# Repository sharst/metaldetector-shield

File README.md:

# metaldetector-shield
Hardware and Software for a custom built metaldetector + pressure sensing shield.
This shield was used in a robotics project for contactless navigation (see https://www.youtube.com/watch?v=rSrG_VnvrPk). 
The hardware and software were jointly developed by Simon Harst and Stefan Brüwer.

## It features:
* connection of up to 8 coils which emit and receive electromagnetical impulses
* connection of up to 8 pressure sensors to detect air pulses
* 24V connection with on-board conversion to 5V for the microcontroller
* on-board CAN-Controller to connect the board to a CAN-bus
* chaining possibility to connect two or more boards together for infinite extension
* a ROS example to use it in your robotics application: [www.github.com/sharst/metaldetector-ros](https://github.com/sharst/metaldetector-ros)

## What you can do with it:
* Contactlessly detect metal objects in the vicinity (distance depends on the coil and object used)
* build a rig of 8, 16 or more coils by chaining several boards together
* detect changes in air pressure (in our case upon collision inside an inflateable bumper)
* send all the information on a CAN or serial bus

The board and all accompanying software is fully open source, so you can get involved, too!

## Hardware setup
### How does this work?
The heart of this shield is an arduino microcontroller, which rapidly triggers 8 rigs of transistors connected to coils. From the impulse of current, the coils generate an electromagnetical impulse. In case there is metal in front of the coil, it will reflect part of the impulse which in turn can be sensed by the coil. The weaker echo of the impulse is again converted to current in the coil, which is measured by an ADC on the board. If you want to see a typical response as measured by the ADC, check out the coil response gif below (--> Configuration files). The board sums up the response. This sum can be used to infer whether a metal object is present and how far away it is.

In addition, the shield can measure impact in terms of air pressure. To do that it constantly measures a rolling average of up to 8 air pressure sensors independently. In case it measures a spike of air pressure above a threshold, it emits a custom message.

This is what needs to be done to get one board running (no chaining):
* Solder at least one sensing coil to the COIL_GND and COIL_0 inputs (for more information, check out --> "A note on the coils"
* (Optionally) connect one BMP180-pressure sensor to one of the pressure inputs
* Connect the arduino on the board to your PC and flash the current firmware
* Set jumper J1 to set the board to MASTER mode
* Set jumper J2 to disable chaining
* In case you do not have a coil/capacitor installed at the 24V input, set jumper J3 to bridge the coil connector
* Connect 24V to one of the 24V ports
* The values of the coils are being output on the serial port now (115200baud)

### To enable chaining
Chaining allows you to connect two boards together. The impulses of the coils will influence one another. Therefore you should not operate two coils close together if you want accurate results. The metaldetector board already takes care that up to 8 coils are fired independently in a row and do not influence each other. If you need more than 8 coils, you can use chaining. Chaining uses an additional signal line between two boards, and the boards will take care to always fire their coils alternatingly.
* Remove jumper J2 to enable chaining
* Set jumper J1 on one board to make it the chaining MASTER. Remove the jumper on all other boards to make them slaves
* You can directly chain the 24V power source as well by connecting the secondary 24V-port to the next board
* Connect to signal wires between the boards. The first one should go from output (>) on board 1 to input (<) on board 2. The second one goes from input (<) on board 1 to output (>) on board 2.
* If you want to connect more than two boards together, connect them in a circle, always taking care that the output goes to the input of the next board, and the input is connected to the output of the previous board.
* If you are using the CAN bus, make sure that the boards are using unique CAN addresses (set them in metaldetector-shield.ino --> TX_CAN_ID and RX_CAN_ID)

### How to produce the boards
* We always ordered our boards at PCB-Pool (in Germany). They accept the kicad-files given in the hardware folder directly as input. 
* You can order the entire BOM on farnell, including the wire for the coils. Check out the BOM in the hardware folder.

### A word on the coils
The coils are key when it comes to which objects can be detected. Here's a few notes:
* The larger the coil diameter, the less focused the impulse will be. In general you get a weaker response with larger coils, but also you cover less area
* We tested both with round and rectangular coils, both worked great.
* The more impedance, the less current flow you will get at the fixed 24V, which means less stronger impulses and responses. But it also means less power consumption.
* The more windings the coil has, the stronger the impulse. But also you will naturally get higher impedance with more windings.
* you will have to experiment to find the best tradeoff for your application. In our case it was a coil from 0.4mm wire with 150 windings equalling to ~11 Ohm.

### A note on the pressure sensors
* We ordered the BMP180 sensors on ebay. Note that there are several versions. The boards we used are 1cm x 1.2cm in size. We hand-crimped the cables to connect them via the JST-plugs.
* If you want to use pressure sensors in an outdoor environment, water resistance is key. We used two cable glands connected together to create an air- and water-tight case. We connected an air tube from the one side which guided the air impulse from the bumper cushion into the case (blue arrow). On the other end we connected the air pressure sensor (red arrow). [See image here.](https://github.com/sharst/metaldetector-shield/blob/master/images/air_pressure_connector.jpg).
* For extra water resistance, it is possible to put the pressure sensor into a ballon before inserting it into the cable gland. [See image here.](https://github.com/sharst/metaldetector-shield/blob/master/images/air_pressure_connector_balloon.jpeg)

## Software setup
We've tried to make the software setup as easy as possible for you. Therefore, all the software needed is bundled in this repository, either directly or by submodules.

### To get the arduino running
```
# Go anywhere where you want to check out this repo
cd ~
git clone https://github.com/sharst/metaldetector-shield
cd metaldetector-shield
# Get all the contained submodules
git submodule init 
git submodule update
# The repository contains an arduino folder. This is basically an arduino sketchbook setup and ready to go. First backup your current one:
mv ~/sketchbook ~/sketchbook_bckp
# Now link the one from the repository with a symbolic link. This means you can still use and manage the repository in the original location, but arduino will find your files.
ln -s ~/metaldetector-shield/arduino ~/sketchbook
```
* Open the arduino IDE (tested with v 1.6.9)
* Select Tools --> Board --> Arduino Nano
* Tools --> Programmer --> AVR ISP
* File --> Open --> ~/sketchbook/arduino/metaldetector_shield.ino
* Upload
* Open Serial Console, set it to 115200 baud, watch the output.

### Overview of the software
./arduino: Contains all the software relevant to the arduino (i.e. the firmware and all libraries)
./PythonLivePlotting: A library to do dynamical plots and updates of figures

#### Configuration files
board_v23.h : Contains mostly pin settings (hardwired on the board, don't change them!). You can also set some identifiers on where pressure and heartbeat signals get send on the CAN-BUS, and the identifier to switch coils.  
metaldetector-shield.ino: The main sketch for upload. Contains some interesting settings:
  * TX_CAN_ID: The CAN ID used for writing messages on the bus. If you are using several boards on the same bus, make sure this is unique for each board.
  * RX_CAN_ID: The ID that this board listens on for messages on the bus. You can dynamically switch some functionalities on the board by sending messages. Make sure this ID is unique for this board.
  * DEBUG: Whether or not to output information on the serial bus.
  * COMM_TIMEOUT: How many ms to wait for a signal from the slave board in chaining mode
  * DEBUG_RAW_ADC_COIL: Only works when DEBUG==true. This will output the raw measurements of the given coil as sampled by the ADC. Run python plot_raw_coil.py to visualize these values. This is a sample output where we approach a metal object to the coil:

  * DEBUG_RAW_PRESSURE: Only works when DEBUG==true. This will output the raw measurements of the given pressure sensor. Run python plot_raw_pressure.py to visualize these values. This is a sample output where we register several bumper hits on the given pressure sensor. In red are detected collisions.

#### Typical operation mode
Check out the loop-function in the main sketch. A loop consists of the following steps:
* If coils are enabled, trigger each coil once and read out the results
* we want to average over several measurements. coil.data_ready() goes to True as soon as we have collected this amount of measurements
* In case some coil data is ready we will output it on the serial bus as a four-byte message, which will be in the format ```[40 (COIL_REGISTER set in board_v23.h), [0-7] (coil_index), highbyte(value), lowbyte(value)]```
* The communication state is toggled so the next board can start measuring
* We now sample the pressure sensors. If one of them transitions a threshold value, we encode this information bitwise. For instance, if pressure sensors 2 and 4 have surpassed the threshold value since the last call, get_bumper_transitions will output 0b00010100 (the second and fourth bit are True).
* We now send out the string "BUMPER" on the serial bus. On the CAN-bus we will send the bitcoded value, this time in the format ```[25 (PRESSURE_REGISTER set in board_v23.h), 0, highbyte(bitcode), lowbyte(bitcode)]```.
* We send out a heartbeat message on the CAN bus. This message contains the information on which ports some pressure sensors are connected and whether the metal sensing functionality is currently switched on. Which ports are currently connected to pressure sensors is again encoded bitwise, i.e. 0b10001001 means that there are sensors connected on the first, fourth and eigth connector on the board. A heartbeat message has the format ```[30 (HEARTBEAT_REGISTER set in board_v23.h), bitwise encoding of connected sensors, (1 or 0 whether coils are enabled)]```

#### Getting the CAN bus running
* In order to interface with a CAN bus from a computer, you typically need a CAN to USB converter. We had some eccellent results with the [USBtin](https://www.fischl.de/usbtin/). It is open source, has a superb interface, a loving maintainer and can be ordered readily assembled.
* In order to connect it, just connect the HIGH, LOW and GND (marked as "T" on the USBtin) lines between the two boards. 
* If you want to connect more metaldetector boards, there are two CAN connectors on each one: One coming in, one going out.
* In addition, you need one termination resistor somewhere on the bus, typically on the last element of the bus chain. If this last element is a metaldetector board, you can simply set jumper J4 to enable the termination resistor.
* Connect the USBTin to your computer, open the interface and set it to 500kbps and see the messages from the board coming in. 
* There is also a ROS driver available which directly interfaces the metaldetector-board to ROS messages [www.github.com/sharst/metaldetector-ros](www.github.com/sharst/metaldetector-ros)

## Summary: Information flow from the metaldetector-shield

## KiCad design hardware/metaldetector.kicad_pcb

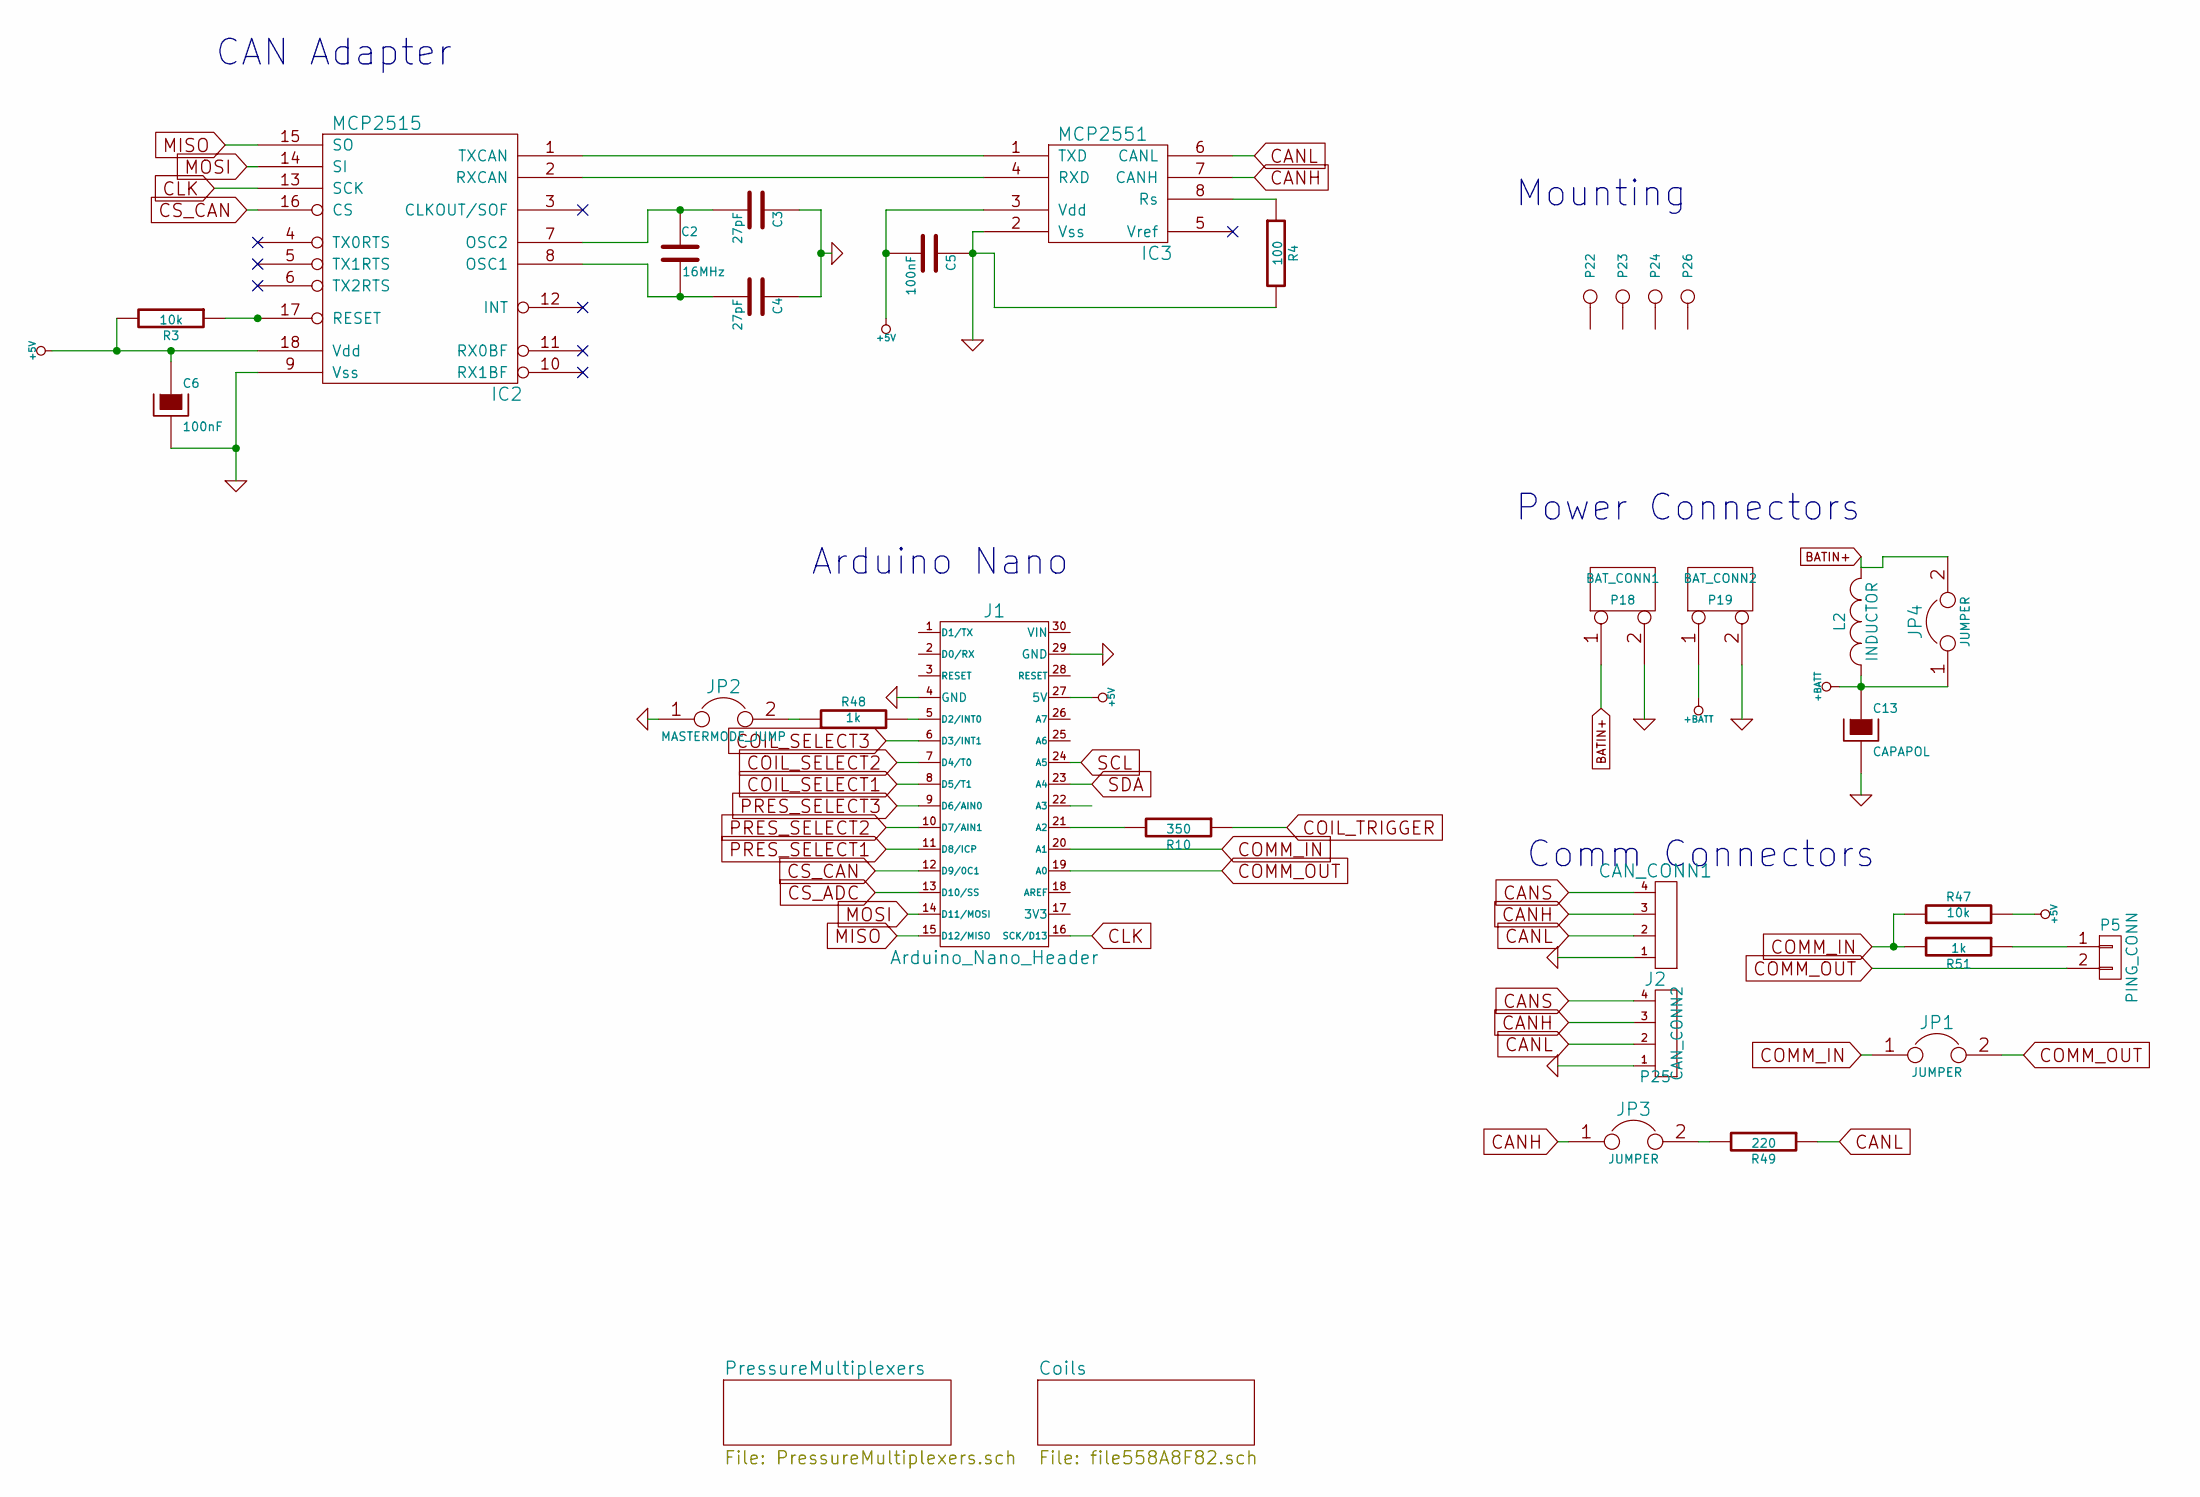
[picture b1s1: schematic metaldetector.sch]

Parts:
C2: 16MHz; HC49SM-Crystal16MHz
C3, C4: 27pF; C_1206_HandSoldering
C5, C6: 100nF; C_1206_HandSoldering
C13: CAPAPOL; C_Radial_D18_L36_P7.5
IC2: MCP2515; SOIC-18_7.5x11.6mm_Pitch1.27mm
IC3: MCP2551; SOIC-8_3.9x4.9mm_Pitch1.27mm
J1: Arduino_Nano_Header; arduino_nano_header
J2: CAN_CONN1; b4b-ph-kl
JP1, JP3, JP4: JUMPER; Socket_Strip_Straight_1x02
JP2: MASTERMODE_JUMP; Socket_Strip_Straight_1x02
L2: INDUCTOR; BOURNS-2324-V-RC
P5: PING_CONN; mkds_1,5-2
P18: BAT_CONN1; mkds_1,5-2
P19: BAT_CONN2; mkds_1,5-2
P22, P23, P24, P26: CONN_1; bore
P25: CAN_CONN2; b4b-ph-kl
R3, R47: 10k; R_1206_HandSoldering
R4: 100; R_1206_HandSoldering
R10: 350; R_1206_HandSoldering
R48, R51: 1k; R_1206_HandSoldering
R49: 220; R_1206_HandSoldering

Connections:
+5V: C5.2, C6.1, IC2.18 (Vdd), IC3.3 (Vdd), J1.27 (5V), R3.2, R47.2; also elsewhere on the board
+BATT: C13.1, JP4.1, L2.1, P19.1; also elsewhere on the board
BATIN+: JP4.2, L2.2, P18.1
CANH: IC3.7 (CANH), J2.3, JP3.1, P25.3
CANL: IC3.6 (CANL), J2.2, P25.2, R49.1
CANS: J2.4, P25.4
CLK: IC2.13 (SCK), J1.16 (SCK/D13); also elsewhere on the board
COIL_SELECT1: J1.8 (D5/T1); also elsewhere on the board
COIL_SELECT2: J1.7 (D4/T0); also elsewhere on the board
COIL_SELECT3: J1.6 (D3/INT1); also elsewhere on the board
COIL_TRIGGER: R10.1; also elsewhere on the board
COMM_IN: J1.20 (A1), JP1.1, R47.1, R51.2
COMM_OUT: J1.19 (A0), JP1.2, P5.2
CS_ADC: J1.13 (D10/SS); also elsewhere on the board
CS_CAN: IC2.16 (CS), J1.12 (D9/0C1)
GND: C3.1, C4.1, C5.1, C6.2, C13.2, IC2.9 (Vss), IC3.2 (Vss), J1.4 (GND), J1.29 (GND), J2.1, JP2.1, P18.2 (PM), P19.2 (PM), P25.1, R4.2; also elsewhere on the board
MISO: IC2.15 (SO), J1.15 (D12/MISO); also elsewhere on the board
MOSI: IC2.14 (SI), J1.14 (D11/MOSI); also elsewhere on the board
unnamed: C2.1, C3.2, IC2.7 (OSC2)
unnamed: C2.2, C4.2, IC2.8 (OSC1)
unnamed: IC2.1 (TXCAN), IC3.1 (TXD)
unnamed: IC2.2 (RXCAN), IC3.4 (RXD)
unnamed: IC2.17 (RESET), R3.1
unnamed: IC3.8 (Rs), R4.1
unnamed: J1.5 (D2/INT0), R48.2
unnamed: J1.21 (A2), R10.2
unnamed: JP2.2, R48.1
unnamed: JP3.2, R49.2
unnamed: P5.1, R51.1
PRES_SELECT1: J1.11 (D8/ICP); also elsewhere on the board
PRES_SELECT2: J1.10 (D7/AIN1); also elsewhere on the board
PRES_SELECT3: J1.9 (D6/AIN0); also elsewhere on the board
SCL: J1.24 (A5); also elsewhere on the board
SDA: J1.23 (A4); also elsewhere on the board

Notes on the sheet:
CAN Adapter
Arduino Nano
Power Connectors
Comm Connectors
Mounting

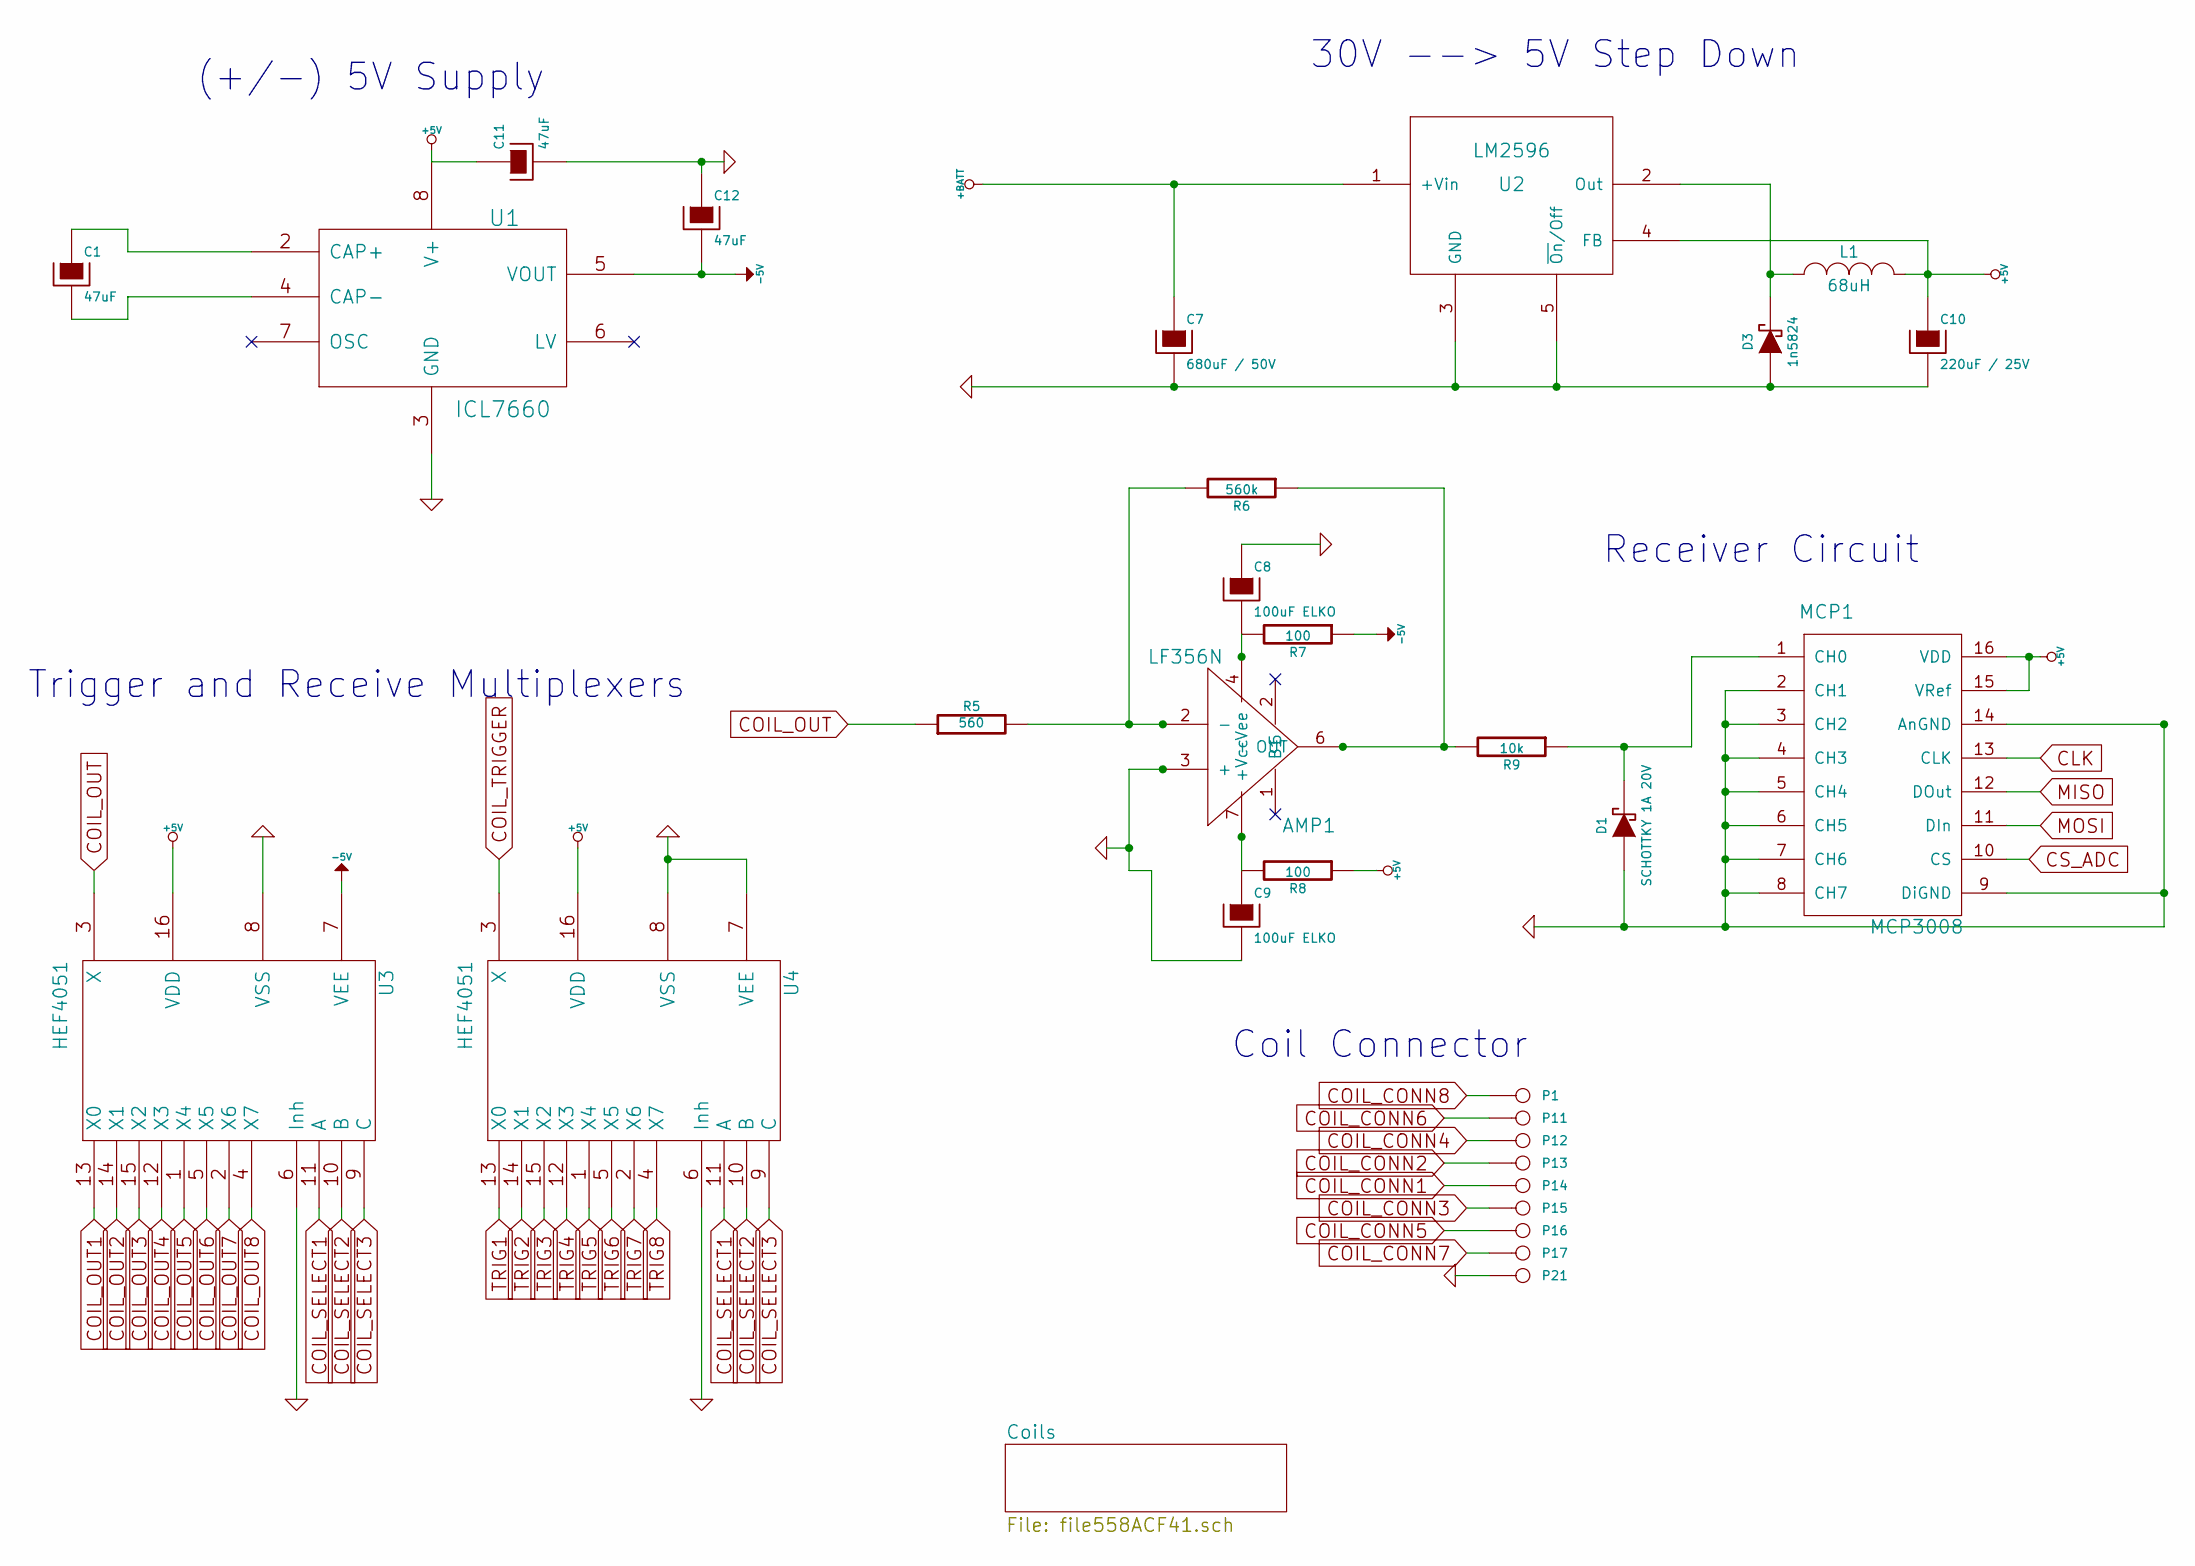
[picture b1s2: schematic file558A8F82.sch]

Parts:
AMP1: LF356N; SOIC-8_3.9x4.9mm_Pitch1.27mm
C1, C11, C12: 47uF; c_elec_6.3x5.3
C7: 680uF / 50V; CAP_D12_5_H13_5_SMD
C8, C9: 100uF ELKO; c_elec_6.3x5.3
C10: 220uF / 25V; c_elec_8x10.5
D1: SCHOTTKY 1A 20V; DO-214AC_Handsoldering
D3: 1n5824; DO-214AB_Handsoldering
L1: 68uH; Ind_68uH
MCP1: MCP3008; SOIC-16_3.9x9.9mm_Pitch1.27mm
P1, P11, P12, P13, P14, P15, P16, P17, P21: CONN_1; solderpad_single
R5: 560; R_1206_HandSoldering
R6: 560k; R_1206_HandSoldering
R7, R8: 100; R_1206_HandSoldering
R9: 10k; R_1206_HandSoldering
U1: ICL7660; SOIC-8_3.9x4.9mm_Pitch1.27mm
U2: LM2596; TO-263-5
U3, U4: HEF4051; SOIC-16_3.9x9.9mm_Pitch1.27mm

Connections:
+5V: C10.1, C11.1, L1.2, MCP1.15 (VRef), MCP1.16 (VDD), R8.1, U1.8 (V+), U2.4 (FB), U3.16 (VDD), U4.16 (VDD); also elsewhere on the board
+BATT: C7.1, U2.1 (+Vin); also elsewhere on the board
-5V: C12.2, R7.1, U1.5 (VOUT), U3.7 (VEE)
CLK: MCP1.13 (CLK); also elsewhere on the board
COIL_CONN1: P14.1; also elsewhere on the board
COIL_CONN2: P13.1; also elsewhere on the board
COIL_CONN3: P15.1; also elsewhere on the board
COIL_CONN4: P12.1; also elsewhere on the board
COIL_CONN5: P16.1; also elsewhere on the board
COIL_CONN6: P11.1; also elsewhere on the board
COIL_CONN7: P17.1; also elsewhere on the board
COIL_CONN8: P1.1; also elsewhere on the board
COIL_OUT: R5.1, U3.3 (X)
COIL_OUT1: U3.13 (X0); also elsewhere on the board
COIL_OUT2: U3.14 (X1); also elsewhere on the board
COIL_OUT3: U3.15 (X2); also elsewhere on the board
COIL_OUT4: U3.12 (X3); also elsewhere on the board
COIL_OUT5: U3.1 (X4); also elsewhere on the board
COIL_OUT6: U3.5 (X5); also elsewhere on the board
COIL_OUT7: U3.2 (X6); also elsewhere on the board
COIL_OUT8: U3.4 (X7); also elsewhere on the board
COIL_SELECT1: U3.11 (A), U4.11 (A); also elsewhere on the board
COIL_SELECT2: U3.10 (B), U4.10 (B); also elsewhere on the board
COIL_SELECT3: U3.9 (C), U4.9 (C); also elsewhere on the board
COIL_TRIGGER: U4.3 (X); also elsewhere on the board
CS_ADC: MCP1.10 (CS); also elsewhere on the board
GND: AMP1.3 (+), C7.2, C8.1, C9.2, C10.2, C11.2, C12.1, D1.1 (A), D3.1 (A), MCP1.2 (CH1), MCP1.3 (CH2), MCP1.4 (CH3), MCP1.5 (CH4), MCP1.6 (CH5), MCP1.7 (CH6), MCP1.8 (CH7), MCP1.9 (DiGND), MCP1.14 (AnGND), P21.1, U1.3 (GND), U2.3 (GND), U2.5 (~On~/Off), U3.6 (Inh), U3.8 (VSS), U4.6 (Inh), U4.7 (VEE), U4.8 (VSS); also elsewhere on the board
MISO: MCP1.12 (DOut); also elsewhere on the board
MOSI: MCP1.11 (DIn); also elsewhere on the board
unnamed: AMP1.2 (-), R5.2, R6.2
unnamed: AMP1.4 (-Vee), C8.2, R7.2
unnamed: AMP1.6 (OUT), R6.1, R9.2
unnamed: AMP1.7 (+Vcc), C9.1, R8.2
unnamed: C1.1, U1.2 (CAP+)
unnamed: C1.2, U1.4 (CAP-)
unnamed: D1.2 (K), MCP1.1 (CH0), R9.1
unnamed: D3.2 (K), L1.1, U2.2 (Out)
TRIG1: U4.13 (X0); also elsewhere on the board
TRIG2: U4.14 (X1); also elsewhere on the board
TRIG3: U4.15 (X2); also elsewhere on the board
TRIG4: U4.12 (X3); also elsewhere on the board
TRIG5: U4.1 (X4); also elsewhere on the board
TRIG6: U4.5 (X5); also elsewhere on the board
TRIG7: U4.2 (X6); also elsewhere on the board
TRIG8: U4.4 (X7); also elsewhere on the board

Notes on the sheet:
30V --> 5V Step Down
(+/-) 5V Supply
Receiver Circuit
Coil Connector
Trigger and Receive Multiplexers

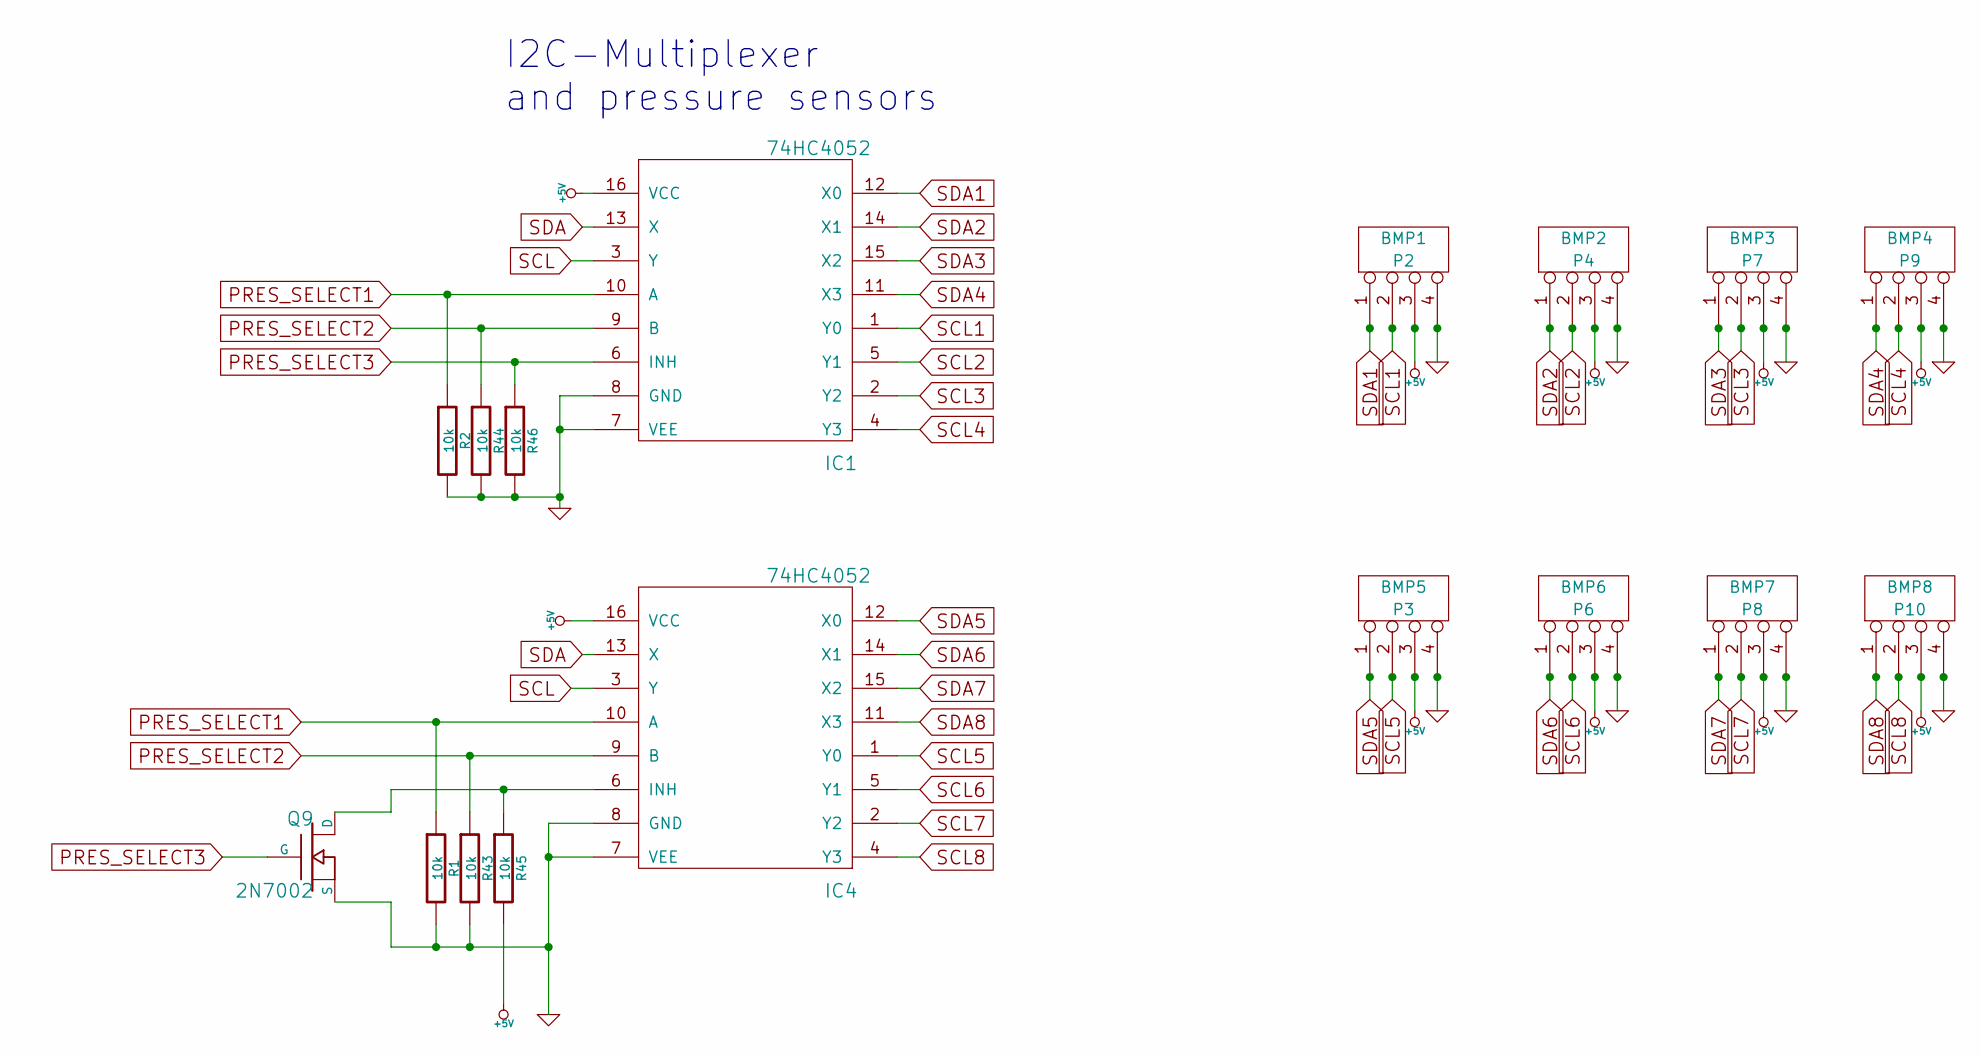
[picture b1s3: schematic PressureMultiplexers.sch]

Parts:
IC1, IC4: 74HC4052; SOIC-16_3.9x9.9mm_Pitch1.27mm
P2: BMP1; b4b-ph-kl
P3: BMP5; b4b-ph-kl
P4: BMP2; b4b-ph-kl
P6: BMP6; b4b-ph-kl
P7: BMP3; b4b-ph-kl
P8: BMP7; b4b-ph-kl
P9: BMP4; b4b-ph-kl
P10: BMP8; b4b-ph-kl
Q9: 2N7002; SOT-23_Handsoldering-MOS-N
R1, R2, R43, R44, R45, R46: 10k; R_1206_HandSoldering

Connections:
+5V: IC1.16 (VCC), IC4.16 (VCC), P2.3, P3.3, P4.3, P6.3, P7.3, P8.3, P9.3, P10.3, R45.2; also elsewhere on the board
GND: IC1.7 (VEE), IC1.8 (GND), IC4.7 (VEE), IC4.8 (GND), P2.4, P3.4, P4.4, P6.4, P7.4, P8.4, P9.4, P10.4, Q9.S, R1.2, R2.2, R43.2, R44.2, R46.2; also elsewhere on the board
unnamed: IC4.6 (INH), Q9.D, R45.1
PRES_SELECT1: IC1.10 (A), IC4.10 (A), R1.1, R2.1; also elsewhere on the board
PRES_SELECT2: IC1.9 (B), IC4.9 (B), R43.1, R44.1; also elsewhere on the board
PRES_SELECT3: IC1.6 (INH), Q9.G, R46.1; also elsewhere on the board
SCL: IC1.3 (Y), IC4.3 (Y); also elsewhere on the board
SCL1: IC1.1 (Y0), P2.2
SCL2: IC1.5 (Y1), P4.2
SCL3: IC1.2 (Y2), P7.2
SCL4: IC1.4 (Y3), P9.2
SCL5: IC4.1 (Y0), P3.2
SCL6: IC4.5 (Y1), P6.2
SCL7: IC4.2 (Y2), P8.2
SCL8: IC4.4 (Y3), P10.2
SDA: IC1.13 (X), IC4.13 (X); also elsewhere on the board
SDA1: IC1.12 (X0), P2.1
SDA2: IC1.14 (X1), P4.1
SDA3: IC1.15 (X2), P7.1
SDA4: IC1.11 (X3), P9.1
SDA5: IC4.12 (X0), P3.1
SDA6: IC4.14 (X1), P6.1
SDA7: IC4.15 (X2), P8.1
SDA8: IC4.11 (X3), P10.1

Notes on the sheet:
I2C-Multiplexer and pressure sensors

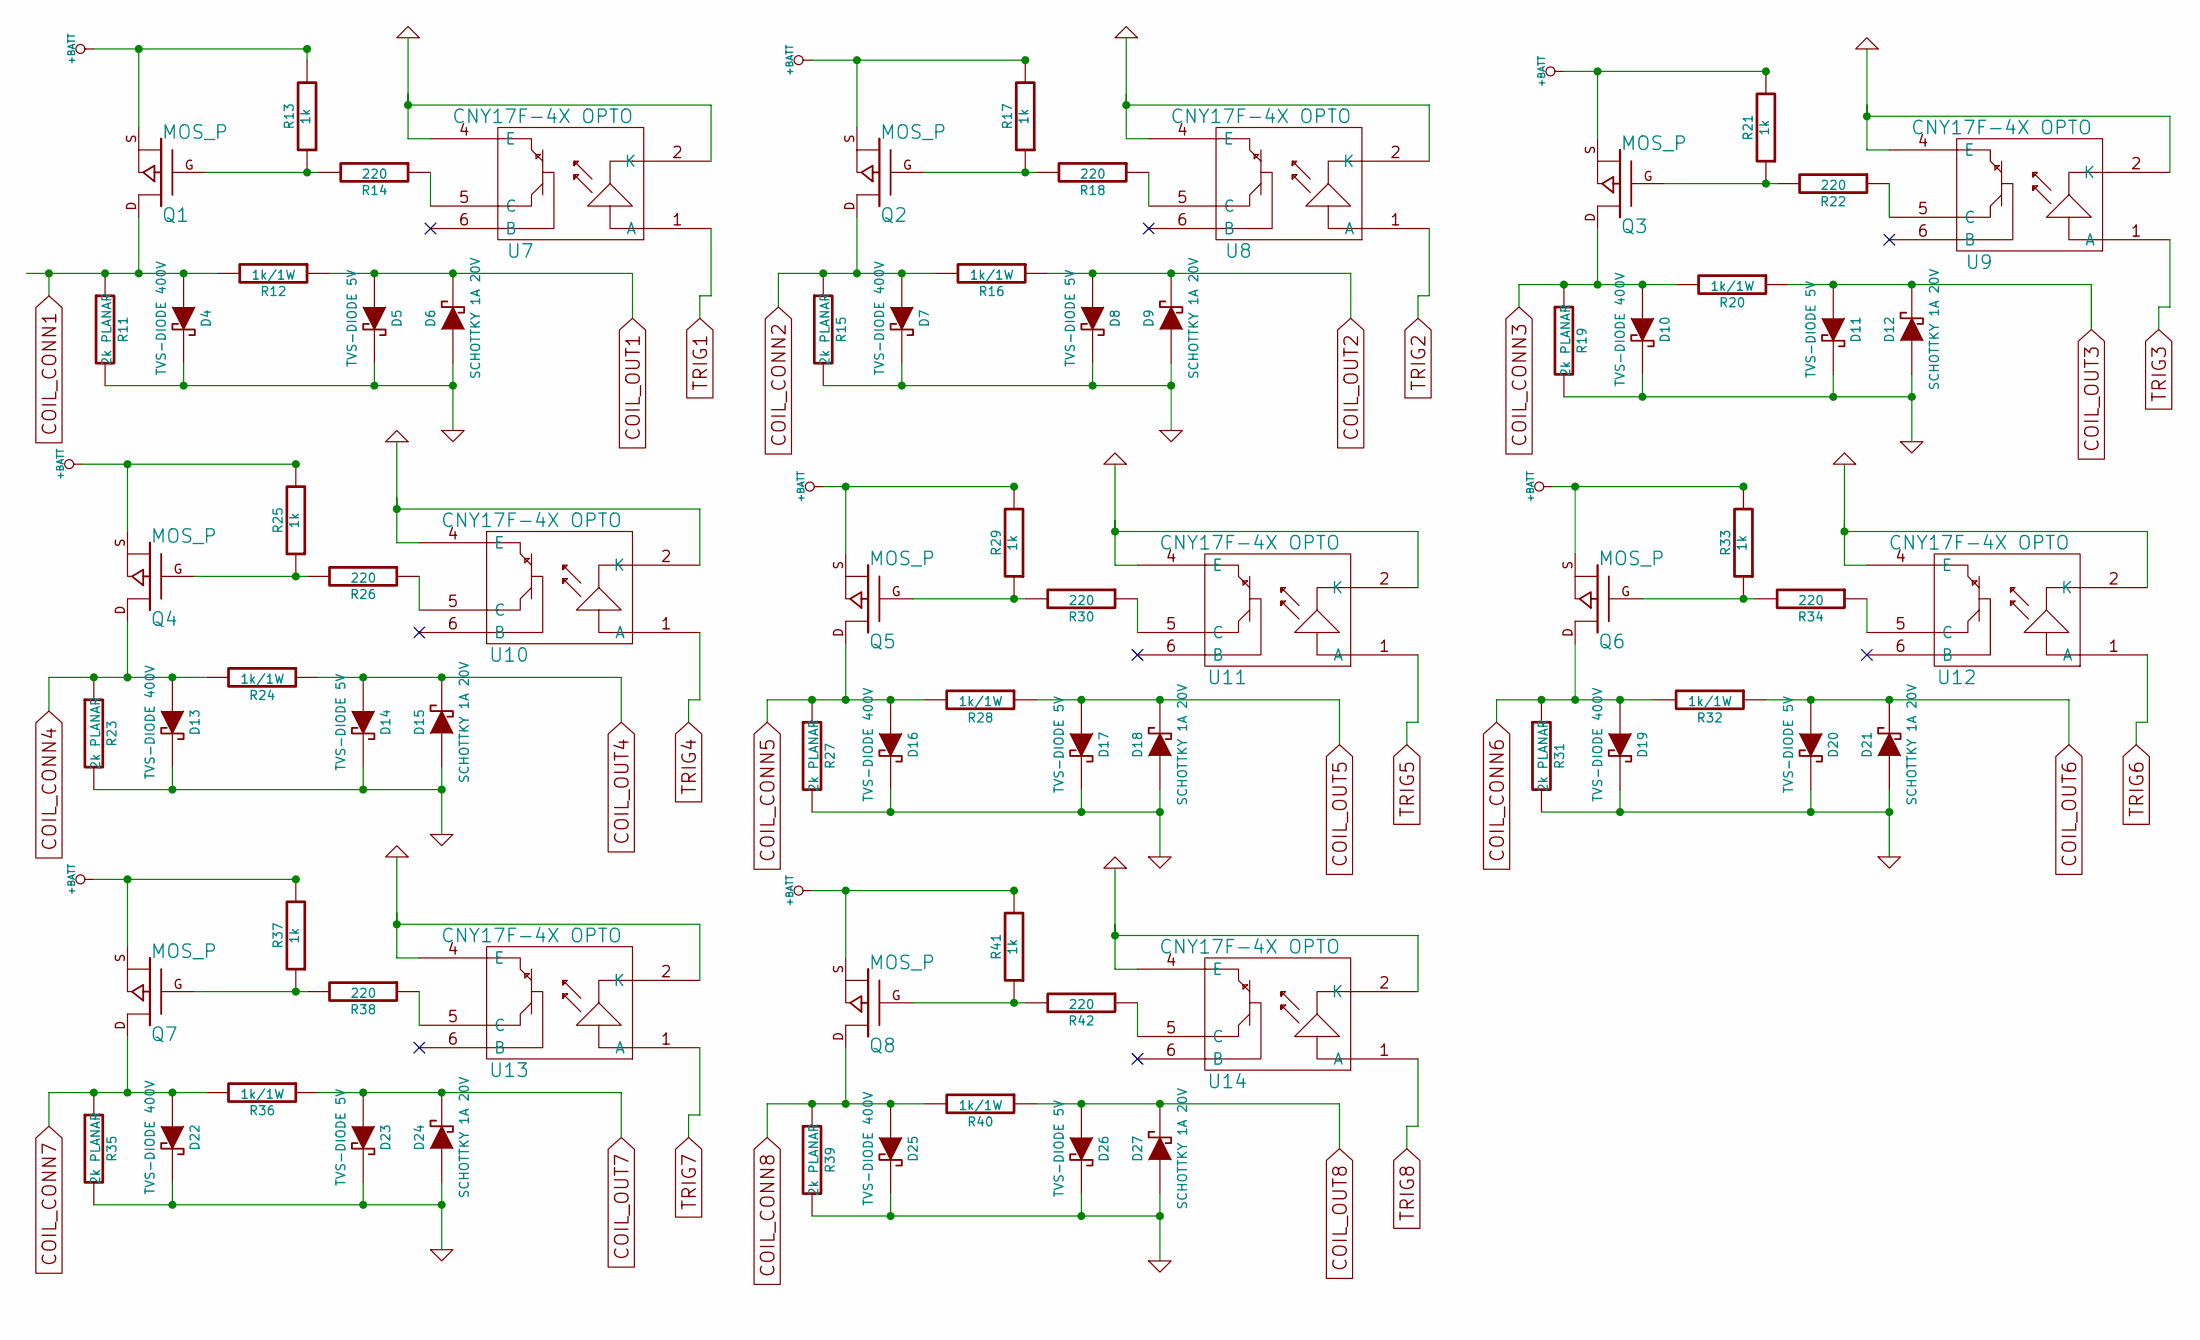
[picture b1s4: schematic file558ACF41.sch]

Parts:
D4, D7, D10, D13, D16, D19, D22, D25: TVS-DIODE 400V; DO-214AC_Handsoldering
D5, D8, D11, D14, D17, D20, D23, D26: TVS-DIODE 5V; Diode-DO-214AB_Handsoldering
D6, D9, D12, D15, D18, D21, D24, D27: SCHOTTKY 1A 20V; DO-214AC_Handsoldering
Q1, Q2, Q3, Q4, Q5, Q6, Q7, Q8: MOS_P; TO-252-3
R11, R15, R19, R23, R27, R31, R35, R39: 2k PLANAR; R_2512_HandSoldering
R12, R16, R20, R24, R28, R32, R36, R40: 1k/1W; R_2512_HandSoldering
R13, R17, R21, R25, R29, R33, R37, R41: 1k; R_1206_HandSoldering
R14, R18, R22, R26, R30, R34, R38, R42: 220; R_1206_HandSoldering
U7, U8, U9, U10, U11, U12, U13, U14: CNY17F-4X OPTO; SMDIP-6

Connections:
+BATT: Q1.S, Q2.S, Q3.S, Q4.S, Q5.S, Q6.S, Q7.S, Q8.S, R13.2, R17.2, R21.2, R25.2, R29.2, R33.2, R37.2, R41.2; also elsewhere on the board
COIL_CONN1: D4.1 (A), Q1.D, R11.1, R12.2; also elsewhere on the board
COIL_CONN2: D7.1 (A), Q2.D, R15.1, R16.2; also elsewhere on the board
COIL_CONN3: D10.1 (A), Q3.D, R19.1, R20.2; also elsewhere on the board
COIL_CONN4: D13.1 (A), Q4.D, R23.1, R24.2; also elsewhere on the board
COIL_CONN5: D16.1 (A), Q5.D, R27.1, R28.2; also elsewhere on the board
COIL_CONN6: D19.1 (A), Q6.D, R31.1, R32.2; also elsewhere on the board
COIL_CONN7: D22.1 (A), Q7.D, R35.1, R36.2; also elsewhere on the board
COIL_CONN8: D25.1 (A), Q8.D, R39.1, R40.2; also elsewhere on the board
COIL_OUT1: D5.1 (A), D6.2 (K), R12.1; also elsewhere on the board
COIL_OUT2: D8.1 (A), D9.2 (K), R16.1; also elsewhere on the board
COIL_OUT3: D11.1 (A), D12.2 (K), R20.1; also elsewhere on the board
COIL_OUT4: D14.1 (A), D15.2 (K), R24.1; also elsewhere on the board
COIL_OUT5: D17.1 (A), D18.2 (K), R28.1; also elsewhere on the board
COIL_OUT6: D20.1 (A), D21.2 (K), R32.1; also elsewhere on the board
COIL_OUT7: D23.1 (A), D24.2 (K), R36.1; also elsewhere on the board
COIL_OUT8: D26.1 (A), D27.2 (K), R40.1; also elsewhere on the board
GND: D4.2 (K), D5.2 (K), D6.1 (A), D7.2 (K), D8.2 (K), D9.1 (A), D10.2 (K), D11.2 (K), D12.1 (A), D13.2 (K), D14.2 (K), D15.1 (A), D16.2 (K), D17.2 (K), D18.1 (A), D19.2 (K), D20.2 (K), D21.1 (A), D22.2 (K), D23.2 (K), D24.1 (A), D25.2 (K), D26.2 (K), D27.1 (A), R11.2, R15.2, R19.2, R23.2, R27.2, R31.2, R35.2, R39.2, U7.2 (K), U7.4 (E), U8.2 (K), U8.4 (E), U9.2 (K), U9.4 (E), U10.2 (K), U10.4 (E), U11.2 (K), U11.4 (E), U12.2 (K), U12.4 (E), U13.2 (K), U13.4 (E), U14.2 (K), U14.4 (E); also elsewhere on the board
unnamed: Q1.G, R13.1, R14.2
unnamed: Q2.G, R17.1, R18.2
unnamed: Q3.G, R21.1, R22.2
unnamed: Q4.G, R25.1, R26.2
unnamed: Q5.G, R29.1, R30.2
unnamed: Q6.G, R33.1, R34.2
unnamed: Q7.G, R37.1, R38.2
unnamed: Q8.G, R41.1, R42.2
unnamed: R14.1, U7.5 (C)
unnamed: R18.1, U8.5 (C)
unnamed: R22.1, U9.5 (C)
unnamed: R26.1, U10.5 (C)
unnamed: R30.1, U11.5 (C)
unnamed: R34.1, U12.5 (C)
unnamed: R38.1, U13.5 (C)
unnamed: R42.1, U14.5 (C)
TRIG1: U7.1 (A); also elsewhere on the board
TRIG2: U8.1 (A); also elsewhere on the board
TRIG3: U9.1 (A); also elsewhere on the board
TRIG4: U10.1 (A); also elsewhere on the board
TRIG5: U11.1 (A); also elsewhere on the board
TRIG6: U12.1 (A); also elsewhere on the board
TRIG7: U13.1 (A); also elsewhere on the board
TRIG8: U14.1 (A); also elsewhere on the board

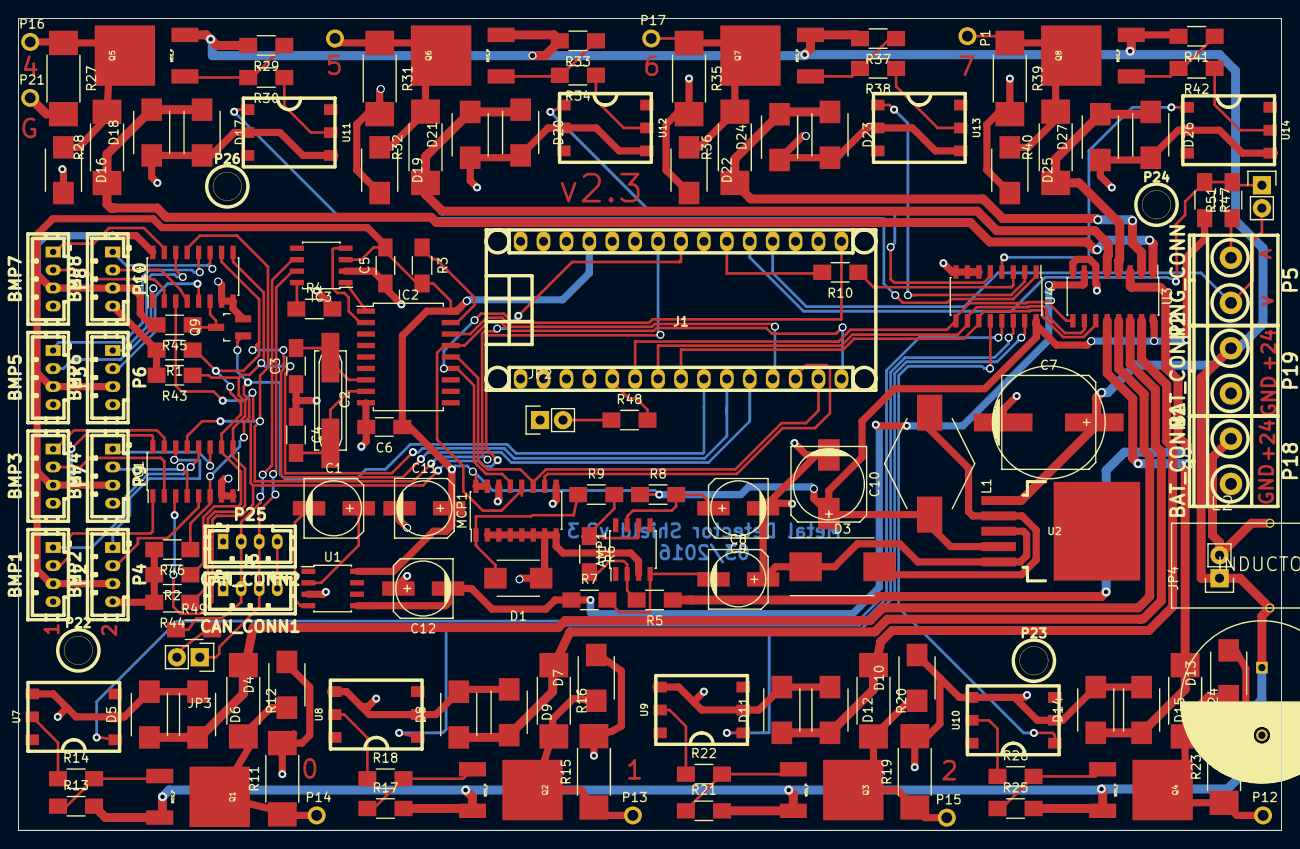
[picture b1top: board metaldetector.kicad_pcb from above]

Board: 2 copper layers, 140.0 x 90.0 mm, 149 parts (1 on the bottom side), 101 nets.

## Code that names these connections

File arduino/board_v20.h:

#ifndef boarddef20_h
#define boarddef20_h

static const byte IS_MASTER =	0;  // 0: SLAVE, 1: MASTER, 2: hardware switch

// Pressure sensor
#define pres_mux1				8
#define pres_mux2				7
#define pres_mux3				6

// Coil sensor
#define coil_adc_cs 		    10
#define coil_select1 			5
#define coil_select2 			4
#define coil_select3 			3
#define coil_trigger 		    A2

// CAN settings
#define can_cs 					9
#define PRESSURE_REGISTER	    25
#define HEARTBEAT_REGISTER		30
#define HEARTBEAT_EVERY			10000

// Ping-Pong settings
#define comm_in					A1
#define comm_out				A0

#define LEDPin					13

#define master_pin				0   // Isn't used when IS_MASTER != 2

#endif
